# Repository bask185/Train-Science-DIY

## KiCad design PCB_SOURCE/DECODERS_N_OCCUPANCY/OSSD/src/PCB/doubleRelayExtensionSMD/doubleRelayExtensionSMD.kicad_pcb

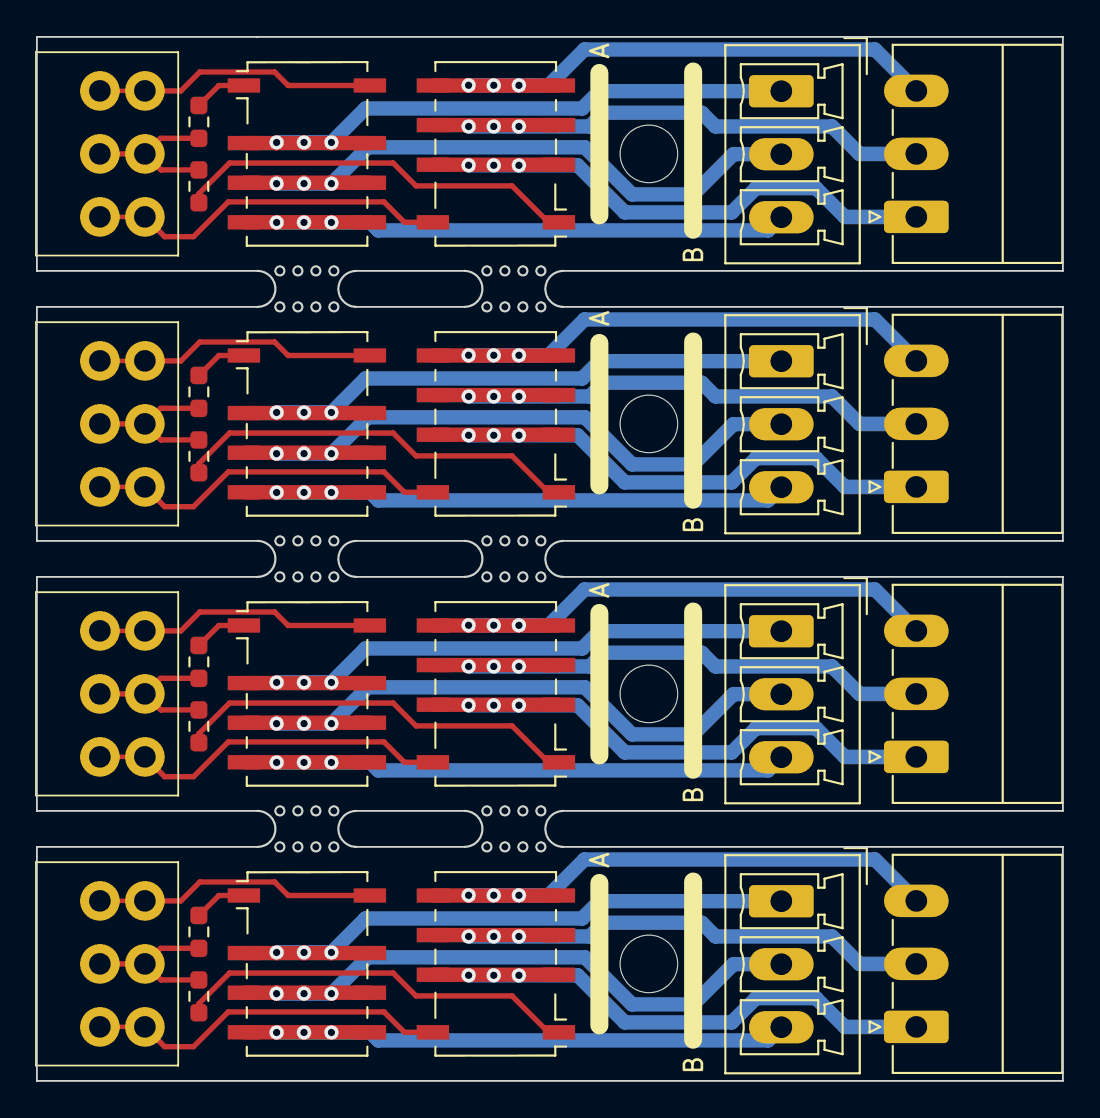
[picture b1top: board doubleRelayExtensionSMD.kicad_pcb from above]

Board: 2 copper layers, 57.0 x 58.0 mm, 28 parts (0 on the bottom side), 44 nets.

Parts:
J1, J2, J7, J10: Screw_Terminal_01x03; connector_3.50mm_3P horizontal_MALE
J3, J4, J8, J11: Screw_Terminal_01x03; PhoenixContact_MC_1,5_3-G-3.5_1x03_P3.50mm_Horizontal
J5, J6, J9, J12: Screw_Terminal_01x03; PhoenixContact_MCV_1,5_3-G-3.5_1x03_P3.50mm_Vertical
K1, K2, K3, K4, K5, K6, K7, K8: G6K-2F-Y-TR DC12; Relay_DPDT_Omron_G6K-2F-Y
R1, R2, R3, R4, R5, R6, R7, R8: 680R; R_0603_smalltext

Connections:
/relay1/Coil1: J1.3, K2.8
/relay1/Coil2: J1.1, K1.8
/relay1/V+: J1.2, R1.2, R2.2
/relay2/Coil1: J2.3, K4.8
/relay2/Coil2: J2.1, K3.8
/relay2/V+: J2.2, R3.2, R4.2
/relay3/Coil1: J7.3, K6.8
/relay3/Coil2: J7.1, K5.8
/relay3/V+: J7.2, R5.2, R6.2
/relay4/Coil1: J10.3, K8.8
/relay4/Coil2: J10.1, K7.8
/relay4/V+: J10.2, R7.2, R8.2
unnamed: J3.1, K3.2, K3.7
unnamed: J3.2, K3.3, K3.6
unnamed: J3.3, K3.4, K3.5
unnamed: J4.1, K1.2, K1.7
unnamed: J4.2, K1.3, K1.6
unnamed: J4.3, K1.4, K1.5
unnamed: J5.1, K2.2, K2.7
unnamed: J5.2, K2.3, K2.6
unnamed: J5.3, K2.4, K2.5
unnamed: J6.1, K4.2, K4.7
unnamed: J6.2, K4.3, K4.6
unnamed: J6.3, K4.4, K4.5
unnamed: J8.1, K5.2, K5.7
unnamed: J8.2, K5.3, K5.6
unnamed: J8.3, K5.4, K5.5
unnamed: J9.1, K6.2, K6.7
unnamed: J9.2, K6.3, K6.6
unnamed: J9.3, K6.4, K6.5
unnamed: J11.1, K7.2, K7.7
unnamed: J11.2, K7.3, K7.6
unnamed: J11.3, K7.4, K7.5
unnamed: J12.1, K8.2, K8.7
unnamed: J12.2, K8.3, K8.6
unnamed: J12.3, K8.4, K8.5
unnamed: K1.1, R1.1
unnamed: K2.1, R2.1
unnamed: K3.1, R3.1
unnamed: K4.1, R4.1
unnamed: K5.1, R5.1
unnamed: K6.1, R6.1
unnamed: K7.1, R7.1
unnamed: K8.1, R8.1

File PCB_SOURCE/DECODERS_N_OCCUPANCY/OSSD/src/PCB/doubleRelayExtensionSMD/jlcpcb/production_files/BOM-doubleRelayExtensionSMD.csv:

Comment,Designator,Footprint,LCSC
680R,"R1,R2,R3,R4,R5,R6,R7,R8",R_0603_smalltext,C17798
Screw_Terminal_01x03,"J12,J5,J6,J9","PhoenixContact_MCV_1,5_3-G-3.5_1x03_P3.50mm_Vertical",C192778
Screw_Terminal_01x03,"J11,J3,J4,J8","PhoenixContact_MC_1,5_3-G-3.5_1x03_P3.50mm_Horizontal",C22380440
G6K-2F-Y-TR DC12,"K1,K2,K3,K4,K5,K6,K7,K8",Relay_DPDT_Omron_G6K-2F-Y,C397192
Screw_Terminal_01x03,"J1,J10,J2,J7",connector_3.50mm_3P horizontal_MALE,C6394074

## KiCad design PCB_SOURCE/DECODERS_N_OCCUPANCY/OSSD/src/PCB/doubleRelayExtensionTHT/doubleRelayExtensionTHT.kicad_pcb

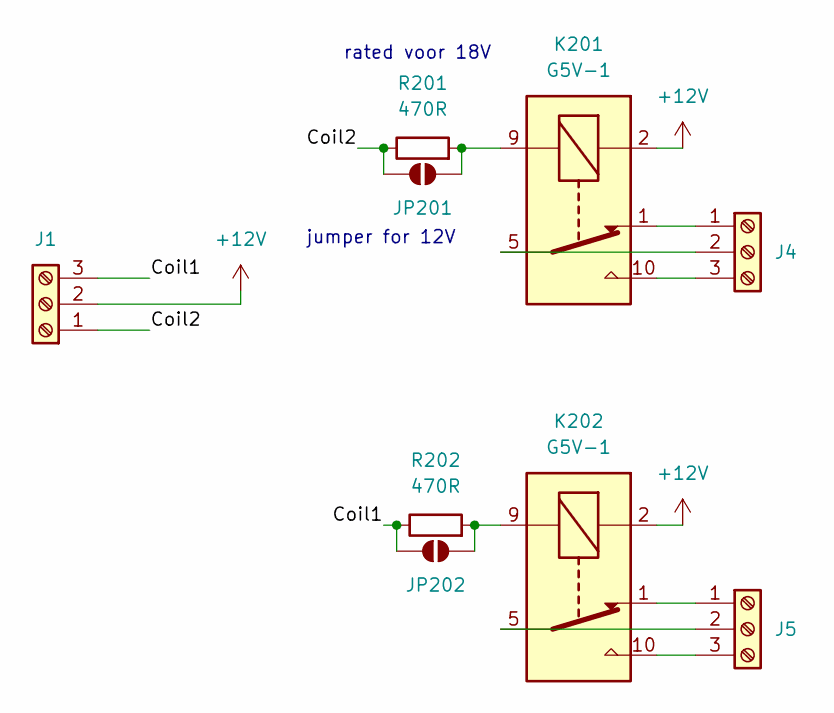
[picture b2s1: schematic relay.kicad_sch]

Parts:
J1: Screw_Terminal_01x03; connector_3.50mm_3P horizontal_MALE; JLCPCB Part# C6394074
J4: Screw_Terminal_01x03; PhoenixContact_MC_1,5_3-G-3.5_1x03_P3.50mm_Horizontal; JLCPCB Part# C22380440
J5: Screw_Terminal_01x03; PhoenixContact_MCV_1,5_3-G-3.5_1x03_P3.50mm_Vertical; Mating Part# C560231; JLCPCB Part# C192778
JP201, JP202: SolderJumper_2_Open; SolderJumper-2_P1.3mm_Open_RoundedPad1.0x1.5mm
K201, K202: G5V-1; Relay_SPDT_Omron_G5V-1
R201, R202: 470R; R_Axial_DIN0204_L3.6mm_D1.6mm_P7.62mm_Horizontal

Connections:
+12V: J1.2, K201.2, K202.2; also elsewhere on the board
/relay1/Coil1: J1.3, JP202.1 (A), R202.1
/relay1/Coil2: J1.1, JP201.1 (A), R201.1
unnamed: J4.1, K201.1
unnamed: J4.2, K201.5, K201.6
unnamed: J4.3, K201.10
unnamed: J5.1, K202.1
unnamed: J5.2, K202.5, K202.6
unnamed: J5.3, K202.10
unnamed: JP201.2 (B), K201.9, R201.2
unnamed: JP202.2 (B), K202.9, R202.2

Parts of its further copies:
J2, J7, J10: Screw_Terminal_01x03; connector_3.50mm_3P horizontal_MALE; JLCPCB Part# C6394074
J3, J8, J11: Screw_Terminal_01x03; PhoenixContact_MC_1,5_3-G-3.5_1x03_P3.50mm_Horizontal; JLCPCB Part# C22380440
J6, J9, J12: Screw_Terminal_01x03; PhoenixContact_MCV_1,5_3-G-3.5_1x03_P3.50mm_Vertical; Mating Part# C560231; JLCPCB Part# C192778
JP301, JP302, JP401, JP402, JP501, JP502: SolderJumper_2_Open; SolderJumper-2_P1.3mm_Open_RoundedPad1.0x1.5mm
K301, K302, K401, K402, K501, K502: G5V-1; Relay_SPDT_Omron_G5V-1
R301, R302, R401, R402, R501, R502: 470R; R_Axial_DIN0204_L3.6mm_D1.6mm_P7.62mm_Horizontal

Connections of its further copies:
+12V: J2.2, J7.2, J10.2, K301.2, K302.2, K401.2, K402.2, K501.2, K502.2; also elsewhere on the board
/relay2/Coil1: J2.3, JP302.1 (A), R302.1
/relay2/Coil2: J2.1, JP301.1 (A), R301.1
/relay3/Coil1: J7.3, JP402.1 (A), R402.1
/relay3/Coil2: J7.1, JP401.1 (A), R401.1
/relay4/Coil1: J10.3, JP502.1 (A), R502.1
/relay4/Coil2: J10.1, JP501.1 (A), R501.1
unnamed: J3.1, K301.1
unnamed: J3.2, K301.5, K301.6
unnamed: J3.3, K301.10
unnamed: J6.1, K302.1
unnamed: J6.2, K302.5, K302.6
unnamed: J6.3, K302.10
unnamed: J8.1, K401.1
unnamed: J8.2, K401.5, K401.6
unnamed: J8.3, K401.10
unnamed: J9.1, K402.1
unnamed: J9.2, K402.5, K402.6
unnamed: J9.3, K402.10
unnamed: J11.1, K501.1
unnamed: J11.2, K501.5, K501.6
unnamed: J11.3, K501.10
unnamed: J12.1, K502.1
unnamed: J12.2, K502.5, K502.6
unnamed: J12.3, K502.10
unnamed: JP301.2 (B), K301.9, R301.2
unnamed: JP302.2 (B), K302.9, R302.2
unnamed: JP401.2 (B), K401.9, R401.2
unnamed: JP402.2 (B), K402.9, R402.2
unnamed: JP501.2 (B), K501.9, R501.2
unnamed: JP502.2 (B), K502.9, R502.2

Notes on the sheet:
jumper for 12V
rated voor 18V

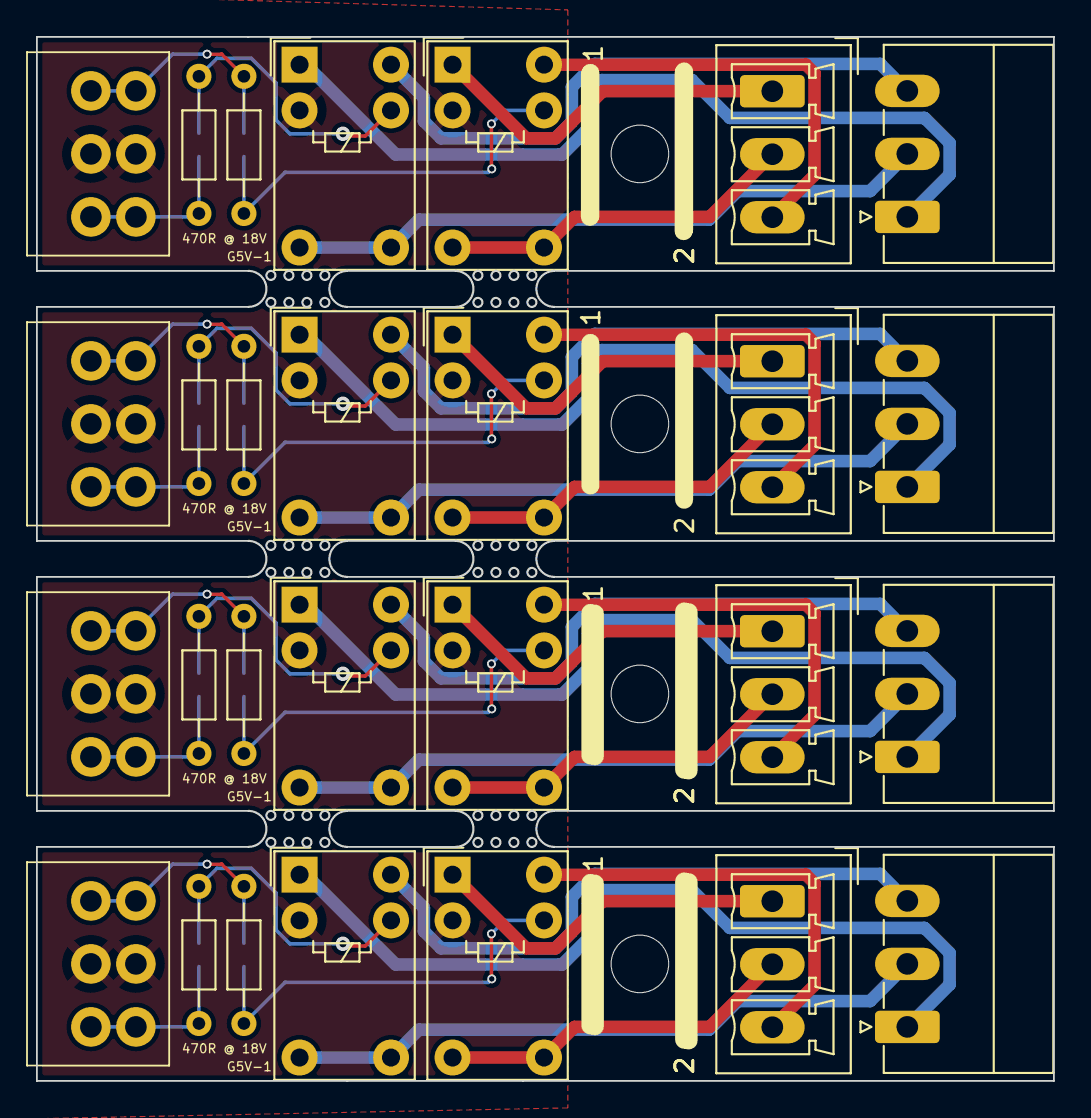
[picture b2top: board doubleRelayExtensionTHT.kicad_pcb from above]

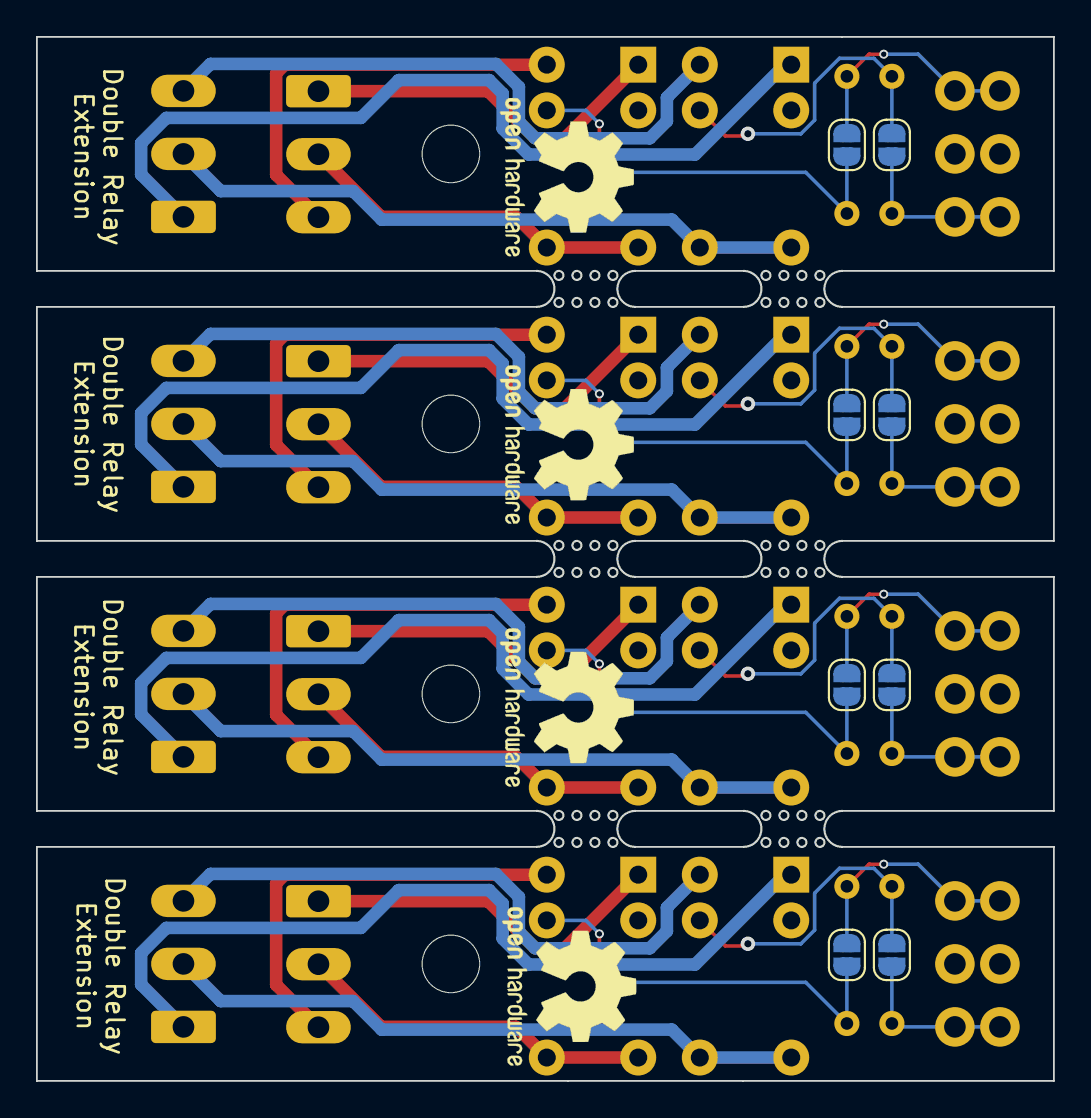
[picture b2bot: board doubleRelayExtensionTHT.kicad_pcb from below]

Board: 2 copper layers, 56.5 x 58.0 mm, 36 parts (8 on the bottom side), 41 nets.

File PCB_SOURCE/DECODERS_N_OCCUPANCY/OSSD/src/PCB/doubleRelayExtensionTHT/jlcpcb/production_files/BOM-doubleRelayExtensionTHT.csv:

Comment,Designator,Footprint,LCSC
Screw_Terminal_01x03,"J12,J5,J6,J9","PhoenixContact_MCV_1,5_3-G-3.5_1x03_P3.50mm_Vertical",C192778
Screw_Terminal_01x03,"J11,J3,J4,J8","PhoenixContact_MC_1,5_3-G-3.5_1x03_P3.50mm_Horizontal",C22380440
Screw_Terminal_01x03,"J1,J10,J2,J7",connector_3.50mm_3P horizontal_MALE,C6394074
470R,R202,R_Axial_DIN0204_L3.6mm_D1.6mm_P7.62mm_Horizontal,
G5V-1,K401,Relay_SPDT_Omron_G5V-1,
G5V-1,K501,Relay_SPDT_Omron_G5V-1,
470R,R501,R_Axial_DIN0204_L3.6mm_D1.6mm_P7.62mm_Horizontal,
G5V-1,K302,Relay_SPDT_Omron_G5V-1,
470R,R502,R_Axial_DIN0204_L3.6mm_D1.6mm_P7.62mm_Horizontal,
G5V-1,K201,Relay_SPDT_Omron_G5V-1,
G5V-1,K301,Relay_SPDT_Omron_G5V-1,
470R,R301,R_Axial_DIN0204_L3.6mm_D1.6mm_P7.62mm_Horizontal,
470R,R302,R_Axial_DIN0204_L3.6mm_D1.6mm_P7.62mm_Horizontal,
G5V-1,K502,Relay_SPDT_Omron_G5V-1,
G5V-1,K402,Relay_SPDT_Omron_G5V-1,
470R,R401,R_Axial_DIN0204_L3.6mm_D1.6mm_P7.62mm_Horizontal,
G5V-1,K202,Relay_SPDT_Omron_G5V-1,
470R,R402,R_Axial_DIN0204_L3.6mm_D1.6mm_P7.62mm_Horizontal,
470R,R201,R_Axial_DIN0204_L3.6mm_D1.6mm_P7.62mm_Horizontal,

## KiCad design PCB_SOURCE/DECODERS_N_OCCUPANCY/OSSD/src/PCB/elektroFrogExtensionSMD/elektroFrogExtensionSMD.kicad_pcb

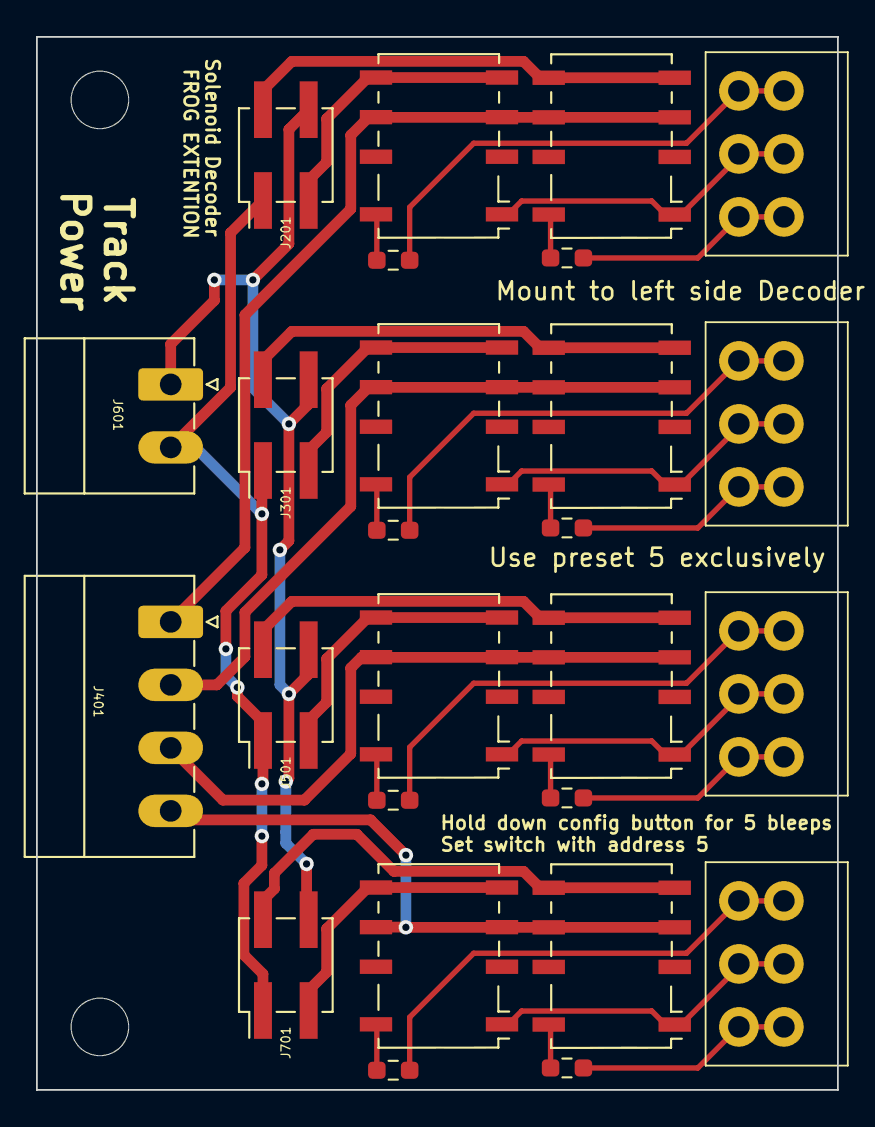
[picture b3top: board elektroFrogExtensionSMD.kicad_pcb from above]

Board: 2 copper layers, 44.5 x 58.5 mm, 26 parts (0 on the bottom side), 31 nets.

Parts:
J201, J301, J501, J701: Conn_02x02_Odd_Even; PinHeader_2x02_P2.54mm_Vertical_SMD
J202, J302, J502, J702: Screw_Terminal_01x03; connector_3.50mm_3P horizontal_MALE
J401: Screw_Terminal_01x04; PhoenixContact_MC_1,5_4-G-3.5_1x04_P3.50mm_Horizontal
J601: Screw_Terminal_01x02; PhoenixContact_MC_1,5_2-G-3.5_1x02_P3.50mm_Horizontal
K201, K202, K301, K302, K501, K502, K701, K702: G6K-2F-Y-TR DC12; Relay_DPDT_Omron_G6K-2F-Y
R201, R202, R301, R302, R501, R502, R701, R702: 680R; R_0603_smalltext

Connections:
+12V: J202.2, J302.2, J502.2, J702.2, K201.1, K202.1, K301.1, K302.1, K501.1, K502.1, K701.1, K702.1
/frog/Frog1: J401.1, K201.3, K201.6, K202.3, K202.6
/frog/Frog2: J401.2, K301.3, K301.6, K302.3, K302.6
/frog/Frog3: J401.3, K501.3, K501.6, K502.3, K502.6
/frog/Frog4: J401.4, K701.3, K701.6, K702.3, K702.6
/relay1/Coil1: J202.3, R201.2
/relay1/Coil2: J202.1, R202.2
/relay2/Coil1: J302.3, R301.2
/relay2/Coil2: J302.1, R302.2
/relay3/Coil1: J502.3, R501.2
/relay3/Coil2: J502.1, R502.2
/relay4/Coil1: J702.3, R701.2
/relay4/Coil2: J702.1, R702.2
DCC_A: J201.1, J301.1, J501.1, J601.2, J701.1
DCC_B: J201.4, J301.4, J501.4, J601.1, J701.4
unnamed: J201.2, K202.4, K202.5
unnamed: J201.3, K201.4, K201.5
unnamed: J301.2, K302.4, K302.5
unnamed: J301.3, K301.4, K301.5
unnamed: J501.2, K502.4, K502.5
unnamed: J501.3, K501.4, K501.5
unnamed: J701.2, K702.4, K702.5
unnamed: J701.3, K701.4, K701.5
unnamed: K201.8, R202.1
unnamed: K202.8, R201.1
unnamed: K301.8, R302.1
unnamed: K302.8, R301.1
unnamed: K501.8, R502.1
unnamed: K502.8, R501.1
unnamed: K701.8, R702.1
unnamed: K702.8, R701.1

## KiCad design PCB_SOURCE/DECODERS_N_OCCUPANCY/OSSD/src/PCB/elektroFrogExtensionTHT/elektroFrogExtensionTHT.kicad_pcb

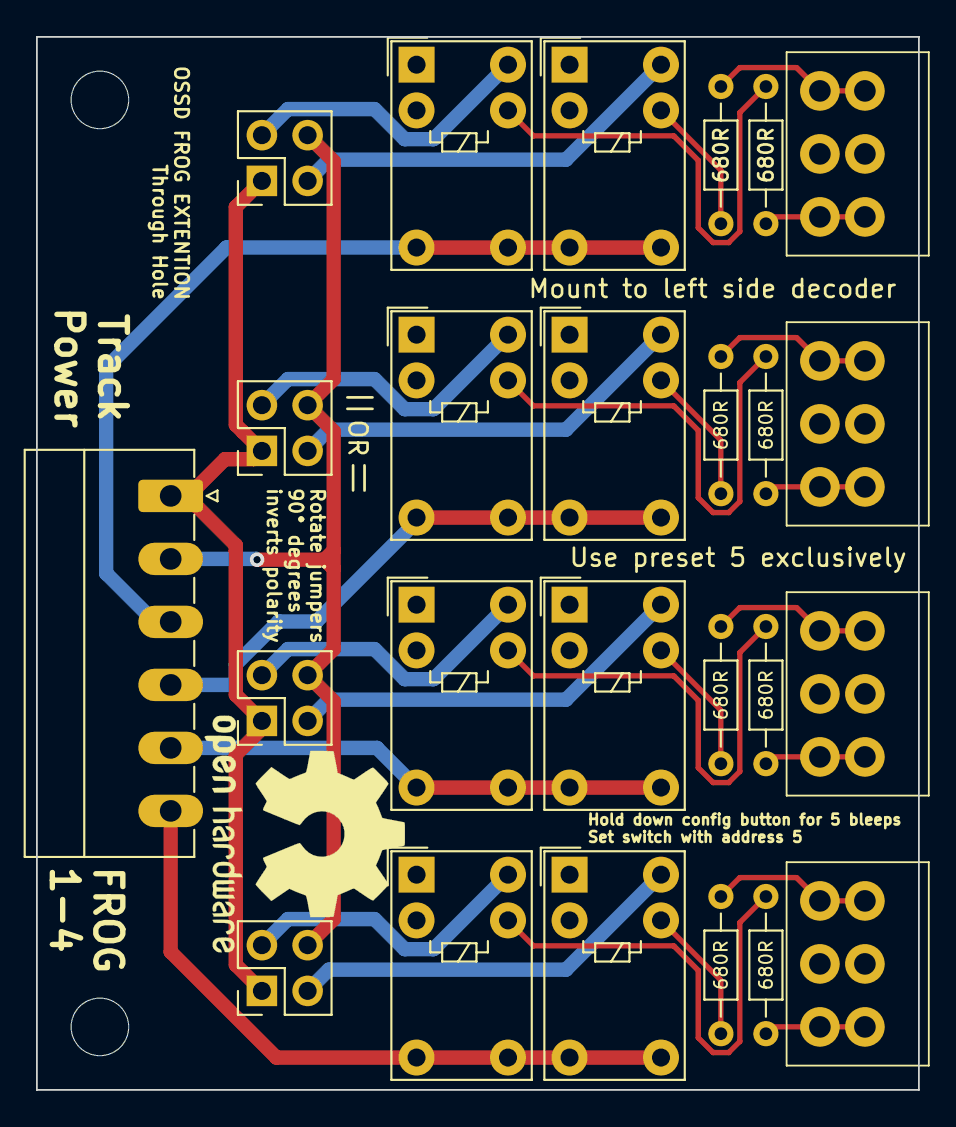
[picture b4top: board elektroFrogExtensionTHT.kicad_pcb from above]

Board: 2 copper layers, 49.0 x 58.5 mm, 25 parts (0 on the bottom side), 31 nets.

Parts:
J201, J301, J501, J701: Conn_02x02_Odd_Even; PinHeader_2x02_P2.54mm_Vertical
J202, J302, J502, J702: Screw_Terminal_01x03; connector_3.50mm_3P horizontal_MALE
J401: Screw_Terminal_01x06; PhoenixContact_MC_1,5_6-G-3.5_1x06_P3.50mm_Horizontal
K1, K2, K3, K4, K5, K6, K7, K8: G5V-1; Relay_SPDT_Omron_G5V-1
R201, R202, R301, R302, R501, R502, R701, R702: 680R; R_Axial_DIN0204_L3.6mm_D1.6mm_P7.62mm_Horizontal

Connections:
+12V: J202.2, J302.2, J502.2, J702.2, K1.2, K2.2, K3.2, K4.2, K5.2, K6.2, K7.2, K8.2
/frog/Frog1: J401.3, K1.5, K1.6, K2.5, K2.6
/frog/Frog2: J401.4, K3.5, K3.6, K4.5, K4.6
/frog/Frog3: J401.5, K5.5, K5.6, K6.5, K6.6
/frog/Frog4: J401.6, K7.5, K7.6, K8.5, K8.6
/relay1/Coil1: J202.3, R201.2
/relay1/Coil2: J202.1, R202.2
/relay2/Coil1: J302.3, R301.2
/relay2/Coil2: J302.1, R302.2
/relay3/Coil1: J502.3, R501.2
/relay3/Coil2: J502.1, R502.2
/relay4/Coil1: J702.3, R701.2
/relay4/Coil2: J702.1, R702.2
DCC_A: J201.1, J301.1, J401.1, J501.1, J701.1
DCC_B: J201.4, J301.4, J401.2, J501.4, J701.4
unnamed: J201.2, K2.10
unnamed: J201.3, K1.10
unnamed: J301.2, K4.10
unnamed: J301.3, K3.10
unnamed: J501.2, K6.10
unnamed: J501.3, K5.10
unnamed: J701.2, K8.10
unnamed: J701.3, K7.10
unnamed: K1.9, R202.1
unnamed: K2.9, R201.1
unnamed: K3.9, R302.1
unnamed: K4.9, R301.1
unnamed: K5.9, R502.1
unnamed: K6.9, R501.1
unnamed: K7.9, R702.1
unnamed: K8.9, R701.1

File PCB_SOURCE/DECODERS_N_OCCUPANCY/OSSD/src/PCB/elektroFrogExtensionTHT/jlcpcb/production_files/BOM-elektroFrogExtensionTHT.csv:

Comment,Designator,Footprint,LCSC
680R,"R201,R202,R301,R302,R501,R502,R701,R702",R_Axial_DIN0204_L3.6mm_D1.6mm_P7.62mm_Horizontal,C17798
Screw_Terminal_01x03,"J202,J302,J502,J702",connector_3.50mm_3P horizontal_MALE,C6394074
Conn_02x02_Odd_Even,"J201,J301,J501,J701",PinHeader_2x02_P2.54mm_Vertical,C919361
G5V-1,K6,Relay_SPDT_Omron_G5V-1,
G5V-1,K5,Relay_SPDT_Omron_G5V-1,
G5V-1,K4,Relay_SPDT_Omron_G5V-1,
Screw_Terminal_01x06,J401,"PhoenixContact_MC_1,5_6-G-3.5_1x06_P3.50mm_Horizontal",
G5V-1,K3,Relay_SPDT_Omron_G5V-1,
G5V-1,K8,Relay_SPDT_Omron_G5V-1,
G5V-1,K2,Relay_SPDT_Omron_G5V-1,
G5V-1,K1,Relay_SPDT_Omron_G5V-1,
G5V-1,K7,Relay_SPDT_Omron_G5V-1,

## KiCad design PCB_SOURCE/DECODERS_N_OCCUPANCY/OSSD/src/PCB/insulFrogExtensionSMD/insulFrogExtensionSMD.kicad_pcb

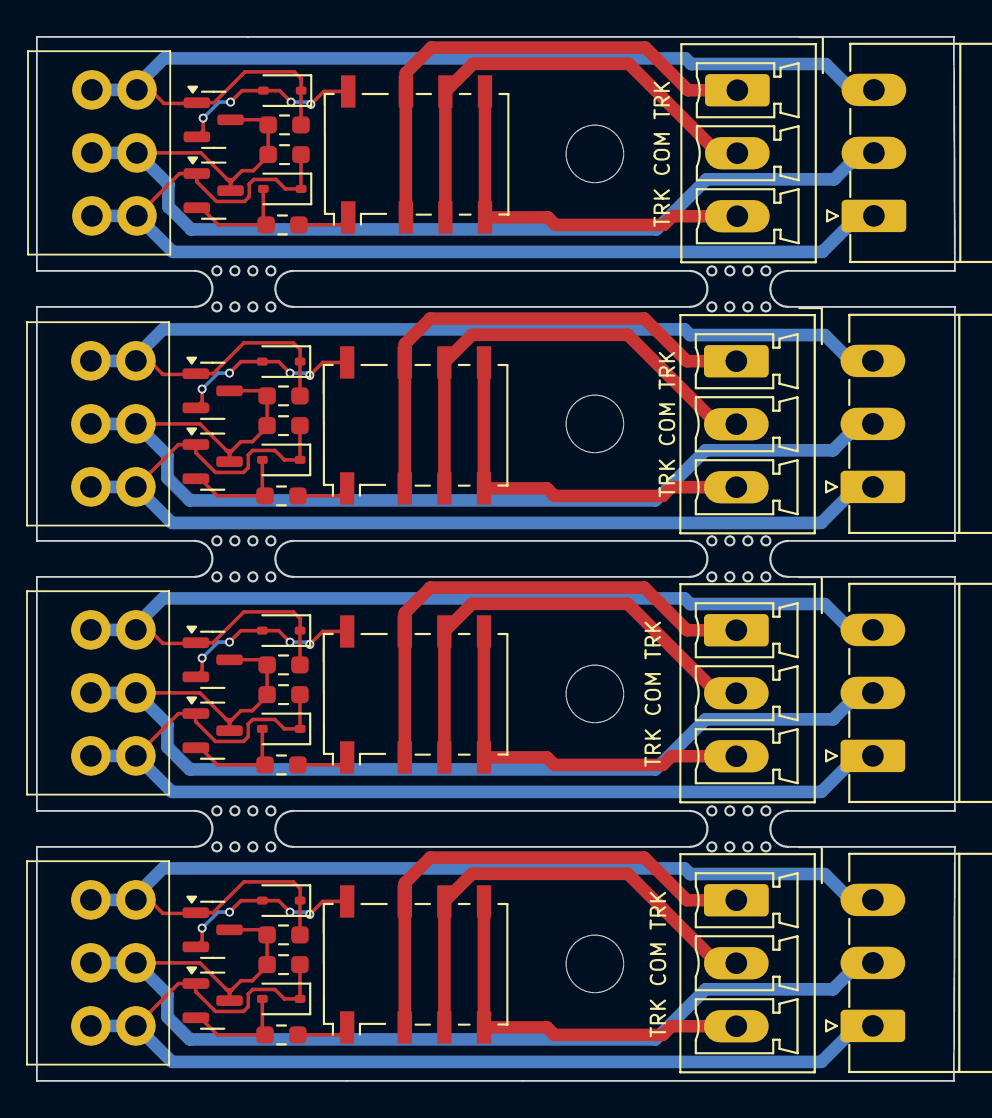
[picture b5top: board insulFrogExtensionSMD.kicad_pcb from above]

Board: 2 copper layers, 51.0 x 58.0 mm, 44 parts (0 on the bottom side), 36 nets.

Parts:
D1, D2, D3, D4, D5, D6, D7, D8: 1N4148WS; D_SOD-323
J1, J2, J7, J10: Screw_Terminal_01x03; connector_3.50mm_3P horizontal_MALE
J3, J4, J8, J11: Screw_Terminal_01x03; PhoenixContact_MC_1,5_3-G-3.5_1x03_P3.50mm_Horizontal
J5, J6, J9, J12: Screw_Terminal_01x03; PhoenixContact_MCV_1,5_3-G-3.5_1x03_P3.50mm_Vertical
K1, K2, K3, K4: G6KU-2; Relay_DPDT_Omron_G6K-2F-Y
Q1, Q2, Q3, Q4, Q5, Q6, Q7, Q8: NPN_TOR; SOT-23
R1, R2, R3, R4, R5, R6, R7, R8: 22k; R_0603_smalltext
R9, R10, R11, R12: 680R; R_0603_smalltext

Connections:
/relay1/DCC_A: J5.1, K1.2, K1.7
/relay1/DCC_B: J5.3, K1.4, K1.5
/relay1/coilA: D2.1 (K), J2.1, J3.1, Q2.1 (B), R2.2
/relay1/coilB: D1.1 (K), J2.3, J3.3, Q1.1 (B), R1.2
/relay1/common: J2.2, J3.2, Q1.3 (C), Q2.3 (C), R1.1, R2.1
/relay2/DCC_A: J6.1, K2.2, K2.7
/relay2/DCC_B: J6.3, K2.4, K2.5
/relay2/coilA: D4.1 (K), J1.1, J4.1, Q4.1 (B), R4.2
/relay2/coilB: D3.1 (K), J1.3, J4.3, Q3.1 (B), R3.2
/relay2/common: J1.2, J4.2, Q3.3 (C), Q4.3 (C), R3.1, R4.1
/relay3/DCC_A: J9.1, K3.2, K3.7
/relay3/DCC_B: J9.3, K3.4, K3.5
/relay3/coilA: D6.1 (K), J7.1, J8.1, Q6.1 (B), R6.2
/relay3/coilB: D5.1 (K), J7.3, J8.3, Q5.1 (B), R5.2
/relay3/common: J7.2, J8.2, Q5.3 (C), Q6.3 (C), R5.1, R6.1
/relay4/DCC_A: J12.1, K4.2, K4.7
/relay4/DCC_B: J12.3, K4.4, K4.5
/relay4/coilA: D8.1 (K), J10.1, J11.1, Q8.1 (B), R8.2
/relay4/coilB: D7.1 (K), J10.3, J11.3, Q7.1 (B), R7.2
/relay4/common: J10.2, J11.2, Q7.3 (C), Q8.3 (C), R7.1, R8.1
unnamed: D1.2 (A), K1.8, Q1.2 (E)
unnamed: D2.2 (A), Q2.2 (E), R9.1
unnamed: D3.2 (A), K2.8, Q3.2 (E)
unnamed: D4.2 (A), Q4.2 (E), R10.1
unnamed: D5.2 (A), K3.8, Q5.2 (E)
unnamed: D6.2 (A), Q6.2 (E), R11.1
unnamed: D7.2 (A), K4.8, Q7.2 (E)
unnamed: D8.2 (A), Q8.2 (E), R12.1
unnamed: J5.2, K1.3, K1.6
unnamed: J6.2, K2.3, K2.6
unnamed: J9.2, K3.3, K3.6
unnamed: J12.2, K4.3, K4.6
unnamed: K1.1, R9.2
unnamed: K2.1, R10.2
unnamed: K3.1, R11.2
unnamed: K4.1, R12.2

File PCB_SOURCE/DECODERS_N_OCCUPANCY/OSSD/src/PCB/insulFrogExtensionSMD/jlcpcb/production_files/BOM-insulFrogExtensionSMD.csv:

Comment,Designator,Footprint,LCSC
680R,"R10,R11,R12,R9",R_0603_smalltext,C17798
1N4148WS,"D1,D2,D3,D4,D5,D6,D7,D8",D_SOD-323,C2128
NPN_TOR,"Q1,Q2,Q3,Q4,Q5,Q6,Q7,Q8",SOT-23,C2145
G6KU-2,"K1,K2,K3,K4",Relay_DPDT_Omron_G6K-2F-Y,C2153173
Screw_Terminal_01x03,"J11,J3,J4,J8","PhoenixContact_MC_1,5_3-G-3.5_1x03_P3.50mm_Horizontal",C22380440
22k,"R1,R2,R3,R4,R5,R6,R7,R8",R_0603_smalltext,C31850
Screw_Terminal_01x03,"J1,J10,J2,J7",connector_3.50mm_3P horizontal_MALE,C6394074
Screw_Terminal_01x03,"J12,J5,J6,J9","PhoenixContact_MCV_1,5_3-G-3.5_1x03_P3.50mm_Vertical",C880555

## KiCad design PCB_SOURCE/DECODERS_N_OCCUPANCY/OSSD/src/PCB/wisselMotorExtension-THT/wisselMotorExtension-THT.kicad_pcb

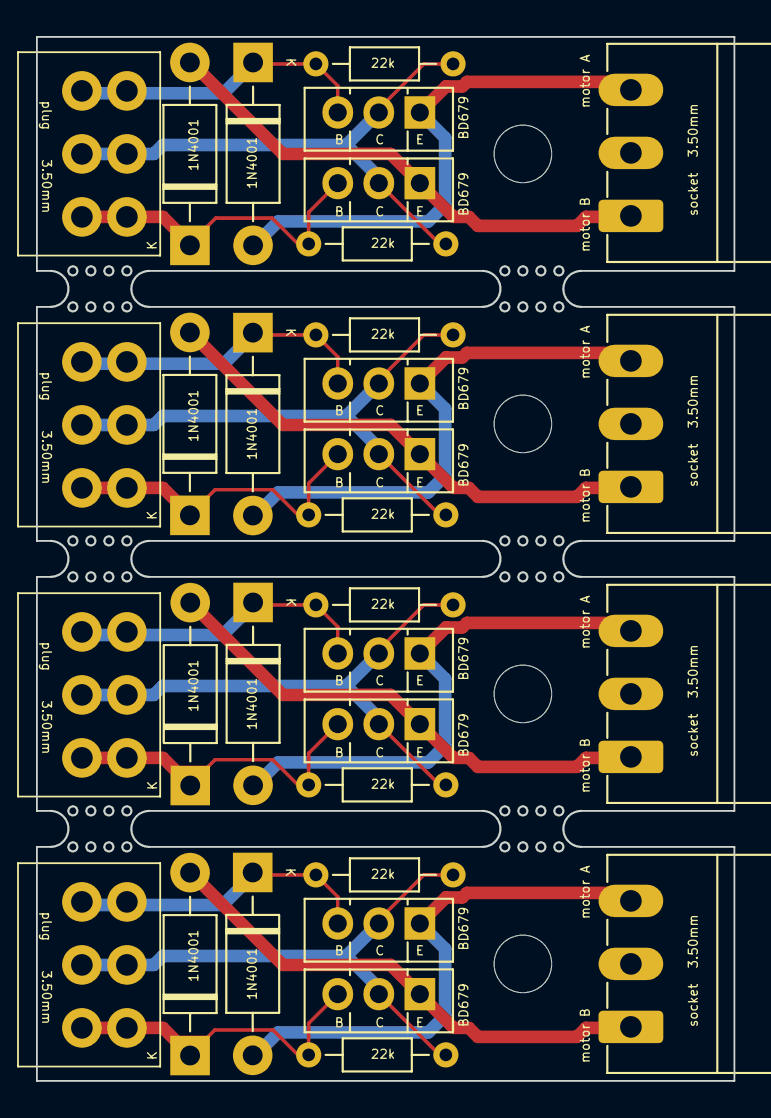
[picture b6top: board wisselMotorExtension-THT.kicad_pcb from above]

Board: 2 copper layers, 38.8 x 58.0 mm, 32 parts (0 on the bottom side), 20 nets.

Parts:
D201, D202, D301, D302, D401, D402, D501, D502: 1N4001; D_DO-41_SOD81_P10.16mm_Horizontal
J201, J301, J401, J501: Screw_Terminal_01x03; connector_3.50mm_3P horizontal_MALE
J202, J302, J402, J502: Screw_Terminal_01x03; PhoenixContact_MC_1,5_3-G-3.5_1x03_P3.50mm_Horizontal
Q201, Q202, Q301, Q302, Q401, Q402, Q501, Q502: BD679; TO-126-3_Vertical
R201, R202, R301, R302, R401, R402, R501, R502: 22k; R_Axial_DIN0204_L3.6mm_D1.6mm_P7.62mm_Horizontal

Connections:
/number 1/coilA: D202.1 (K), J201.3, Q202.3 (B), R202.2
/number 1/coilB: D201.1 (K), J201.1, Q201.3 (B), R201.2
/number 1/collector: J201.2, Q201.2 (C), Q202.2 (C), R201.1, R202.1
/number 1/motA: D202.2 (A), J202.3, Q202.1 (E)
/number 1/motB: D201.2 (A), J202.1, Q201.1 (E)
/number 2/coilA: D302.1 (K), J301.3, Q302.3 (B), R302.2
/number 2/coilB: D301.1 (K), J301.1, Q301.3 (B), R301.2
/number 2/collector: J301.2, Q301.2 (C), Q302.2 (C), R301.1, R302.1
/number 2/motA: D302.2 (A), J302.3, Q302.1 (E)
/number 2/motB: D301.2 (A), J302.1, Q301.1 (E)
/number 3/coilA: D402.1 (K), J401.3, Q402.3 (B), R402.2
/number 3/coilB: D401.1 (K), J401.1, Q401.3 (B), R401.2
/number 3/collector: J401.2, Q401.2 (C), Q402.2 (C), R401.1, R402.1
/number 3/motA: D402.2 (A), J402.3, Q402.1 (E)
/number 3/motB: D401.2 (A), J402.1, Q401.1 (E)
/number 4/coilA: D502.1 (K), J501.3, Q502.3 (B), R502.2
/number 4/coilB: D501.1 (K), J501.1, Q501.3 (B), R501.2
/number 4/collector: J501.2, Q501.2 (C), Q502.2 (C), R501.1, R502.1
/number 4/motA: D502.2 (A), J502.3, Q502.1 (E)
/number 4/motB: D501.2 (A), J502.1, Q501.1 (E)

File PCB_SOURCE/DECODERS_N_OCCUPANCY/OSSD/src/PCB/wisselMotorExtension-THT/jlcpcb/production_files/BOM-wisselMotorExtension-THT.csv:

Comment,Designator,Footprint,LCSC
Screw_Terminal_01x03,"J202,J302,J402,J502","PhoenixContact_MC_1,5_3-G-3.5_1x03_P3.50mm_Horizontal",C22380440
Screw_Terminal_01x03,"J201,J301,J401,J501",connector_3.50mm_3P horizontal_MALE,C6394074
22k,R502,R_Axial_DIN0204_L3.6mm_D1.6mm_P7.62mm_Horizontal,
22k,R501,R_Axial_DIN0204_L3.6mm_D1.6mm_P7.62mm_Horizontal,
22k,R402,R_Axial_DIN0204_L3.6mm_D1.6mm_P7.62mm_Horizontal,
22k,R401,R_Axial_DIN0204_L3.6mm_D1.6mm_P7.62mm_Horizontal,
22k,R302,R_Axial_DIN0204_L3.6mm_D1.6mm_P7.62mm_Horizontal,
22k,R301,R_Axial_DIN0204_L3.6mm_D1.6mm_P7.62mm_Horizontal,
22k,R202,R_Axial_DIN0204_L3.6mm_D1.6mm_P7.62mm_Horizontal,
22k,R201,R_Axial_DIN0204_L3.6mm_D1.6mm_P7.62mm_Horizontal,
BD679,Q502,TO-126-3_Vertical,
BD679,Q501,TO-126-3_Vertical,
BD679,Q402,TO-126-3_Vertical,
BD679,Q401,TO-126-3_Vertical,
BD679,Q302,TO-126-3_Vertical,
BD679,Q301,TO-126-3_Vertical,
BD679,Q202,TO-126-3_Vertical,
BD679,Q201,TO-126-3_Vertical,
1N4001,D502,D_DO-41_SOD81_P10.16mm_Horizontal,
1N4001,D501,D_DO-41_SOD81_P10.16mm_Horizontal,
1N4001,D402,D_DO-41_SOD81_P10.16mm_Horizontal,
1N4001,D401,D_DO-41_SOD81_P10.16mm_Horizontal,
1N4001,D302,D_DO-41_SOD81_P10.16mm_Horizontal,
1N4001,D301,D_DO-41_SOD81_P10.16mm_Horizontal,
1N4001,D202,D_DO-41_SOD81_P10.16mm_Horizontal,
1N4001,D201,D_DO-41_SOD81_P10.16mm_Horizontal,
